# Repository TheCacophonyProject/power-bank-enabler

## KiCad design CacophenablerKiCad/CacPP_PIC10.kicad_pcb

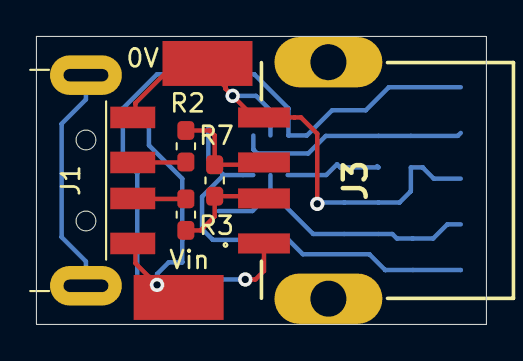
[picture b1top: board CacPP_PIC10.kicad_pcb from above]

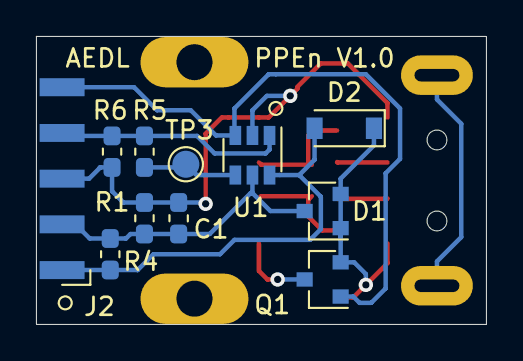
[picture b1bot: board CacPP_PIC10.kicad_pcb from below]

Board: 2 copper layers, 25.0 x 16.0 mm, 18 parts (11 on the bottom side), 12 nets.

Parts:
0V: 0V_in; SolderWirePad_1x01_SMD_1.5x5mm
C1: 1uF 10V; C_0603_1608Metric_Pad1.05x0.95mm_HandSolder
D1: BAT54C; SOT-23
D2: 1N4148; D_SOD-123
J1: USB_A; USB_A_Molex_48037_2200
J2: ICSP interface; Harwin_M20-89005xx_1x05_P2.54mm_Horizontal
J3: 2410_06
Q1: FDN340P; SOT-23
R1: 4M7; R_0603_1608Metric_Pad1.05x0.95mm_HandSolder
R2, R3: 0 NF; R_0603_1608Metric_Pad1.05x0.95mm_HandSolder
R4, R5: 10K NF; R_0603_1608Metric_Pad1.05x0.95mm_HandSolder
R6: 100K; R_0603_1608Metric_Pad1.05x0.95mm_HandSolder
R7: 200; R_0603_1608Metric_Pad1.05x0.95mm_HandSolder
TP3: Debug; TestPoint_Pad_D1.5mm
U1: PIC10F220-IOT; SOT-23-6
Vin: Vin; SolderWirePad_1x01_SMD_1.5x5mm

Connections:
/AN0: J2.4, R5.2, R6.1, U1.1
/DEBUG: R5.1, TP3.1, U1.4
/ICSPCLK: J2.5, Q1.1, U1.3
/MCLR: D2.2, J2.1, R4.1, U1.6
/VCC: C1.1, D1.3, J2.2, R1.1, R4.2, U1.5
/Vin: D1.1, D1.2, D2.1, J1.1, Q1.2, Vin.1
/Vout: J3.1, Q1.3
GND: 0V.1, C1.2, J1.4, J2.3, J3.4, R1.2, R6.2, U1.2
unnamed: J1.2, R3.2
unnamed: J1.3, R2.2
unnamed: J3.2, R3.1, R7.1
unnamed: J3.3, R2.1, R7.2

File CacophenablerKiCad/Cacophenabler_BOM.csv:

Ref,Footprint,Description,$unit,Comments
U1,SOT23-6,PIC10F220_I/OT2,$0.92,program at J2 via spring loaded test pins
Q1,SOT23-3,pFET FDN340P or FDN338P1,$0.51,
D1,SOT23-3,dual Schottky CC BAT54C,$0.08,
D2,SOD123,1N4148,$0.16,Fit D2 after programming PIC
R1,603,4M7,$0.00,NF
R2,603,0R NF,$0.00,NF
R3,603,0R NF,$0.00,NF
R4,603,10K NF,$0.00,NF
R5,603,10K NF,$0.00,NF
R6,603,33K,$0.01,Selects 24 hour cycle
R7,603,200R,$0.01,
C1,603,1uF 10V MLCC,$0.08,
J1,xxx,USB plug Molex 48037-2200,$2.06,
J2,xxx,ICSP pads,$0.00,pads for programming
J3,xxx,USB sck Lumberg 2410-06,$1.33,
,,,,
Component cost / unit,,,$5.16,
,,,,
PCB cost (PCBcart),,,,
40 boards = USD47.53 = NZ$74.53,,,,
PCB cost / board,,,$1.86,
,,,,
Heatshrink 19mm black ~$10/m,,,,
Need ~25mm / unit,,,$0.25,
,,,,
Total parts cost / unit,,,$7.27,
,,,,
Manufacture cost,,,,
"(hand assemble, program, test)",,,,
estimate 10min/board,,,,
Allowance only,,,$10.00,
,,,,
Total manufactured cost / unit,,,$17.27,

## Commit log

2019-10-01 initial version
